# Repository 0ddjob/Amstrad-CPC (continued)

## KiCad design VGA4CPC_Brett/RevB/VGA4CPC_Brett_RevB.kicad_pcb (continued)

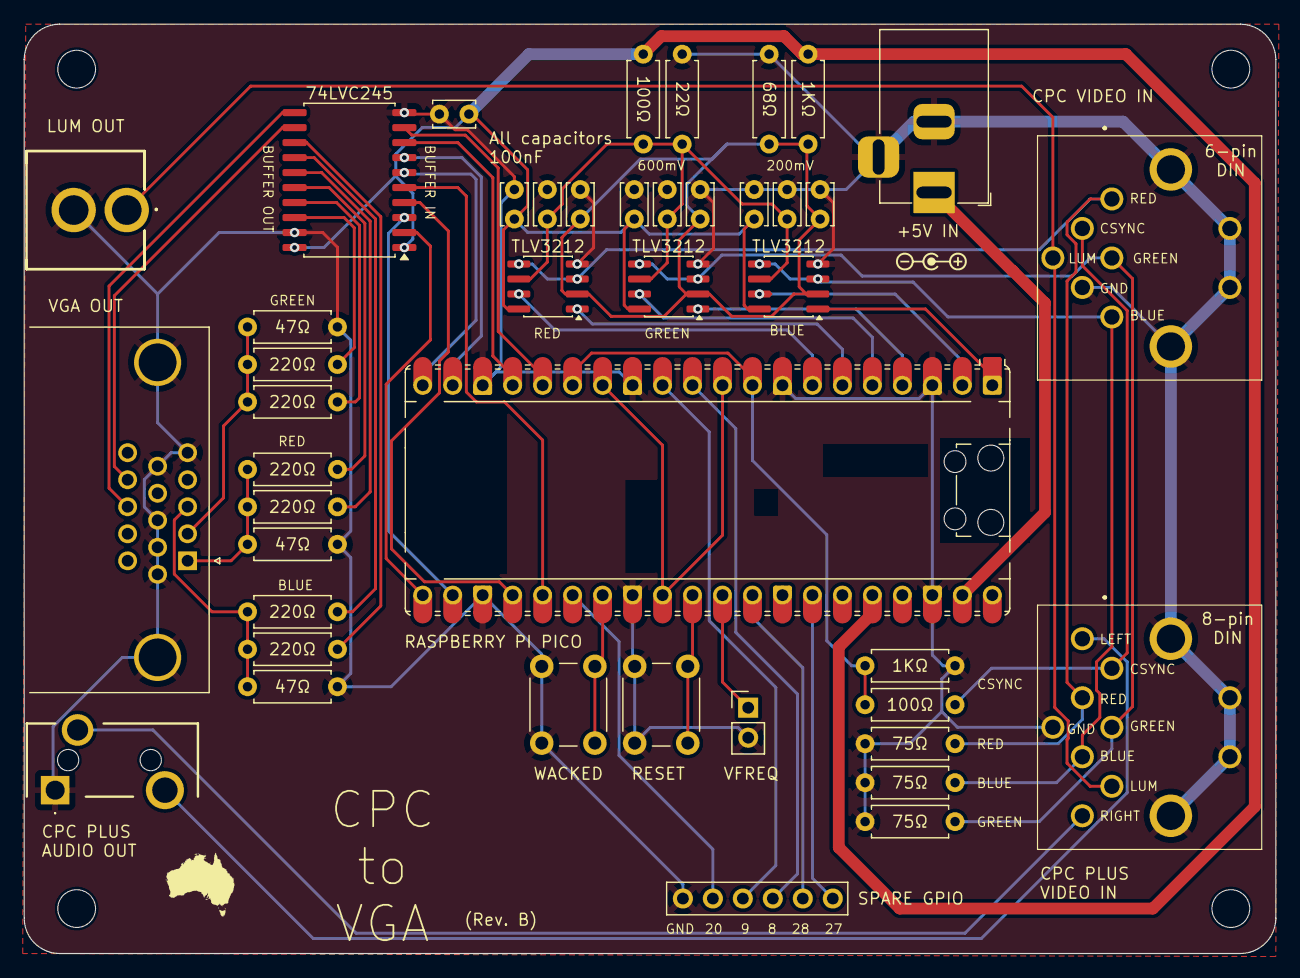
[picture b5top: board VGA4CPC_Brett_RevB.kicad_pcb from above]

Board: 2 copper layers, 106.0 x 78.7 mm, 47 parts (0 on the bottom side), 47 nets.

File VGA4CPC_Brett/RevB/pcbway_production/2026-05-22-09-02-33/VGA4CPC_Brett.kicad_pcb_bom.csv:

Designator,Quantity,Value,Footprint,Package,MPN,DNP,Mount_Type,Description,Height,Mouser Part Number,Mouser Price/Stock,Manufacturer_Name
"C1, C10, C2, C3, C4, C5, C6, C7, C8, C9",10,100nF,C_Disc_D3.4mm_W2.1mm_P2.50mm,,,,tht,,,,,
"H1, H2, H3, H4",4,MountingHole,MountingHole_3.2mm_M3,,,,tht,,,,,
J1,1,+5V IN,BarrelJack_Horizontal,,,,tht,DC Barrel Jack,,,,
J2,1,CPC PLUS AUDIO OUT,SJ335083ATR,,,,tht,"Audio Jack, 3 Poles (Stereo / TRS)",,,,
J3,1,CPC PLUS VIDEO IN,SDF80J,,,,tht,Same Sky SDF-80J 8-pin DIN socket,,,,
J4,1,CPC VIDEO IN,SDF80J,,,,tht,Same Sky SDF-60J 6-pin DIN Socket,,,,
J5,1,VFREQ,PinHeader_1x02_P2.54mm_Vertical,,,,tht,"Generic connector, single row, 01x02, script generated (kicad-library-utils/schlib/autogen/connector/)",,,,
J6,1,VGA OUT,DSUB-15-HD_Socket_Horizontal_P2.29x2.54mm_EdgePinOffset8.35mm_Housed_MountingHolesOffset10.89mm,,,,tht,"15-pin D-SUB connector, socket (female), High density (3 columns), Triple Row, Generic, VGA-connector, Mounting Hole",,,,
J7,1,LUM OUT,1560099E,,,,tht,"coaxial connector (BNC, SMA, SMB, SMC, Cinch/RCA, LEMO, ...)",,,,
"R1, R7",2,1KΩ,R_Axial_DIN0207_L6.3mm_D2.5mm_P7.62mm_Horizontal,,,,tht,"Resistor, small symbol",,,,
"R10, R12, R13, R15, R16, R18",6,220Ω,R_Axial_DIN0207_L6.3mm_D2.5mm_P7.62mm_Horizontal,,,,tht,"Resistor, small symbol",,,,
"R11, R14, R17",3,47Ω,R_Axial_DIN0207_L6.3mm_D2.5mm_P7.62mm_Horizontal,,,,tht,"Resistor, small symbol",,,,
"R2, R6",2,100Ω,R_Axial_DIN0207_L6.3mm_D2.5mm_P7.62mm_Horizontal,,,,tht,"Resistor, small symbol",,,,
R3,1,68Ω,R_Axial_DIN0207_L6.3mm_D2.5mm_P7.62mm_Horizontal,,,,tht,"Resistor, small symbol",,,,
R4,1,22Ω,R_Axial_DIN0207_L6.3mm_D2.5mm_P7.62mm_Horizontal,,,,tht,"Resistor, small symbol",,,,
"R5, R8, R9",3,75Ω,R_Axial_DIN0207_L6.3mm_D2.5mm_P7.62mm_Horizontal,,,,tht,"Resistor, small symbol",,,,
SW1,1,RESET,SW_PUSH_6mm,,,,tht,"Push button switch, generic, two pins",,,,
"U1, U2, U4",3,TLV3202AID,SOIC-8_3.9x4.9mm_P1.27mm,,TLV3202AID,,smt,"Dual, 40ns, microPower, Rail-to-Rail input  Comparator with Push-pull outputs",1.75,595-TLV3202AID,https://www.mouser.co.uk/ProductDetail/Texas-Instruments/TLV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,Texas Instruments
U3,1,RASPBERRY PI PICO,RaspberryPi_Pico_Common_Unspecified,,,,tht,"Versatile and inexpensive microcontroller module powered by RP2040 dual-core Arm Cortex-M0+ processor up to 133 MHz, 264kB SRAM, 2MB QSPI flash; also supports Raspberry Pi Pico 2",,,,
U5,1,74LVC245,SOIC-20W_7.5x12.8mm_P1.27mm,,,,smt,"Octal BUS Transceivers, 3-State outputs",,,,

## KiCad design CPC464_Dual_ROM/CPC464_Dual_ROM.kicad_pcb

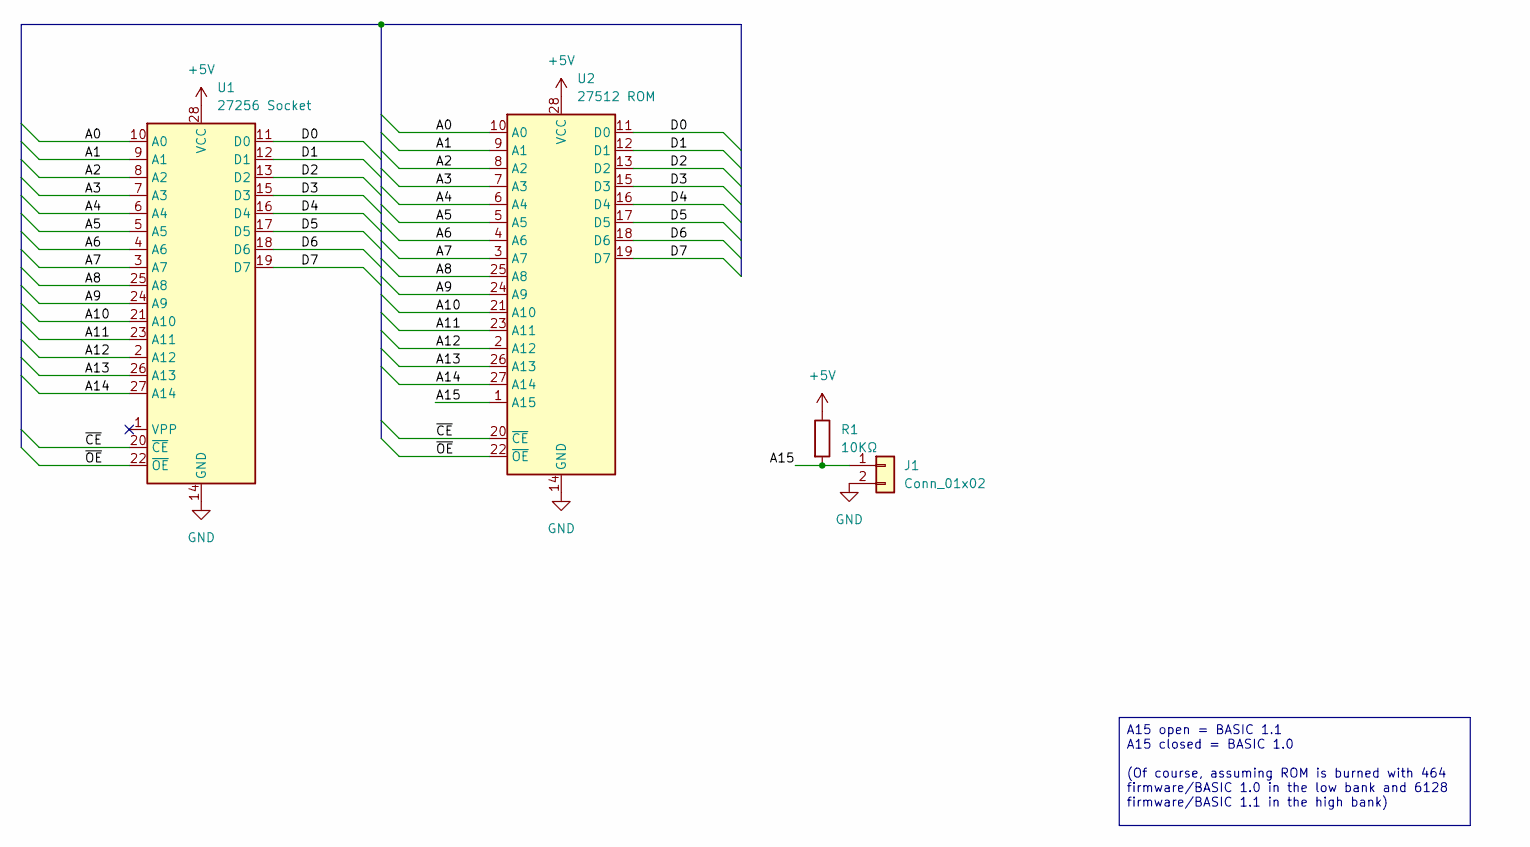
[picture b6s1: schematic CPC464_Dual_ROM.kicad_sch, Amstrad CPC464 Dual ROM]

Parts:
J1: Conn_01x02; PinHeader_1x02_P2.54mm_Vertical
R1: 10KΩ; R_Axial_DIN0207_L6.3mm_D2.5mm_P7.62mm_Horizontal
U1: 27256 Socket; DIP-28_W15.24mm
U2: 27512 ROM; DIP-28_W15.24mm_Socket

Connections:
+5V: R1.1, U1.28 (VCC), U2.28 (VCC)
/A0: U1.10 (A0), U2.10 (A0)
/A1: U1.9 (A1), U2.9 (A1)
/A2: U1.8 (A2), U2.8 (A2)
/A3: U1.7 (A3), U2.7 (A3)
/A4: U1.6 (A4), U2.6 (A4)
/A5: U1.5 (A5), U2.5 (A5)
/A6: U1.4 (A6), U2.4 (A6)
/A7: U1.3 (A7), U2.3 (A7)
/A8: U1.25 (A8), U2.25 (A8)
/A9: U1.24 (A9), U2.24 (A9)
/A10: U1.21 (A10), U2.21 (A10)
/A11: U1.23 (A11), U2.23 (A11)
/A12: U1.2 (A12), U2.2 (A12)
/A13: U1.26 (A13), U2.26 (A13)
/A14: U1.27 (A14), U2.27 (A14)
/A15: J1.1, R1.2, U2.1 (A15)
/D0: U1.11 (D0), U2.11 (D0)
/D1: U1.12 (D1), U2.12 (D1)
/D2: U1.13 (D2), U2.13 (D2)
/D3: U1.15 (D3), U2.15 (D3)
/D4: U1.16 (D4), U2.16 (D4)
/D5: U1.17 (D5), U2.17 (D5)
/D6: U1.18 (D6), U2.18 (D6)
/D7: U1.19 (D7), U2.19 (D7)
/~CE: U1.20 (~CE), U2.20 (~CE)
/~OE: U1.22 (~OE), U2.22 (~OE)
GND: J1.2, U1.14 (GND), U2.14 (GND)

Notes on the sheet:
A15 open = BASIC 1.1 A15 closed = BASIC 1.0 (Of course, assuming ROM is burned with 464 firmware/BASIC 1.0 in the low bank and 6128 firmware/BASIC 1.1 in the high bank)

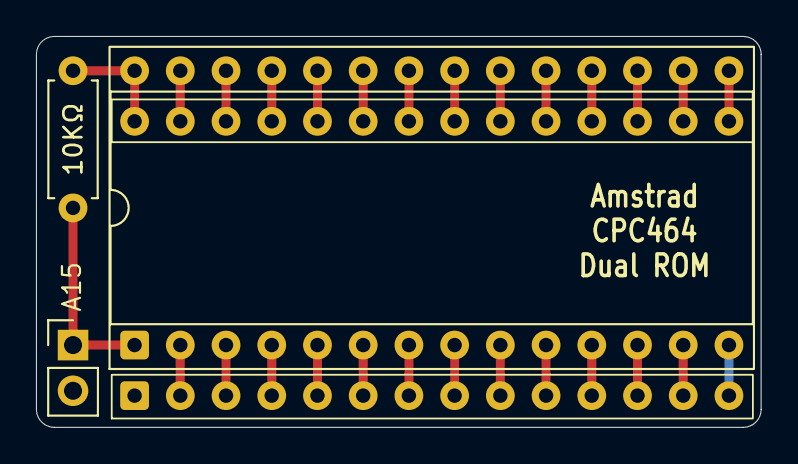
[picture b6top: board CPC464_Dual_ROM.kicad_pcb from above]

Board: 2 copper layers, 40.3 x 21.7 mm, 4 parts (0 on the bottom side), 28 nets.

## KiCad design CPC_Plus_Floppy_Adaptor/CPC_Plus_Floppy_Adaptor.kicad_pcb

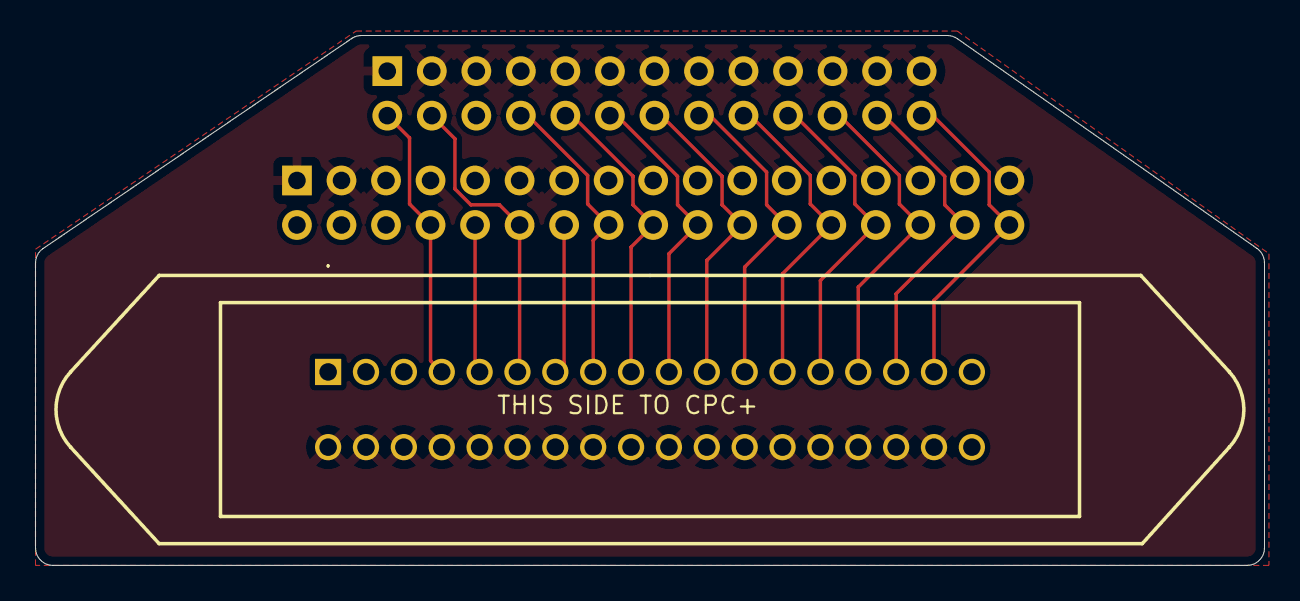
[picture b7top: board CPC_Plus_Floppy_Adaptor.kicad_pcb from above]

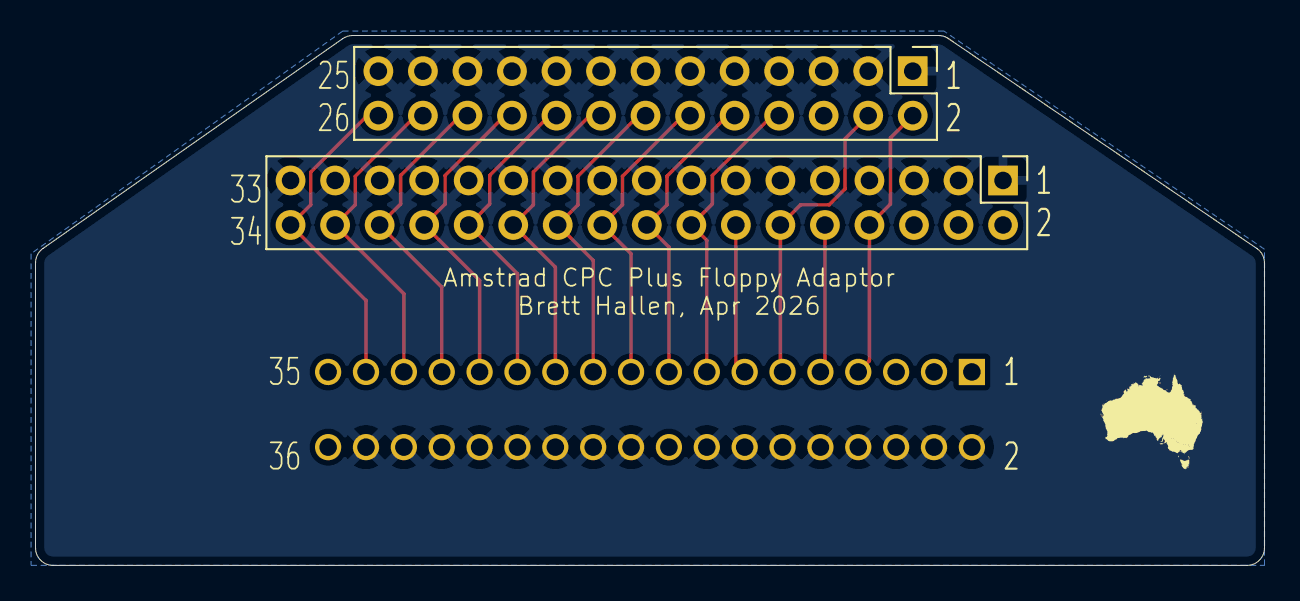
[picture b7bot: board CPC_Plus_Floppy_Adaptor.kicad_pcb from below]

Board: 2 copper layers, 70.1 x 30.2 mm, 3 parts (2 on the bottom side), 15 nets.

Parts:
J1: 111-036-113L001
J2: Standard Floppy; PinHeader_2x17_P2.54mm_Vertical
J3: CPC Floppy; PinHeader_2x13_P2.54mm_Vertical

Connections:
/~DIR: J1.17, J2.18, J3.10
/~DRVSA: J1.13, J2.14
/~DRVSB: J1.11, J2.12, J3.4
/~INDEX: J1.7, J2.8, J3.2
/~MOTEA: J1.9, J2.10
/~MOTEB: J1.15, J2.16, J3.8
/~RDATA: J1.29, J2.30, J3.22
/~RDY: J1.33, J2.34, J3.26
/~SIDE1: J1.31, J2.32, J3.24
/~STEP: J1.19, J2.20, J3.12
/~TRK00: J1.25, J2.26, J3.18
/~WDATA: J1.21, J2.22, J3.14
/~WGATE: J1.23, J2.24, J3.16
/~WPT: J1.27, J2.28, J3.20
GND: J1.2, J1.4, J1.6, J1.8, J1.10, J1.12, J1.14, J1.16, J1.20, J1.22, J1.24, J1.26, J1.28, J1.30, J1.32, J1.34, J2.1, J2.3, J2.5, J2.7, J2.9, J2.11, J2.13, J2.15, J2.17, J2.19, J2.21, J2.23, J2.25, J2.27, J2.29, J2.31, J2.33, J3.1, J3.3, J3.5, J3.7, J3.9, J3.11, J3.13, J3.15, J3.17, J3.19, J3.21, J3.23, J3.25

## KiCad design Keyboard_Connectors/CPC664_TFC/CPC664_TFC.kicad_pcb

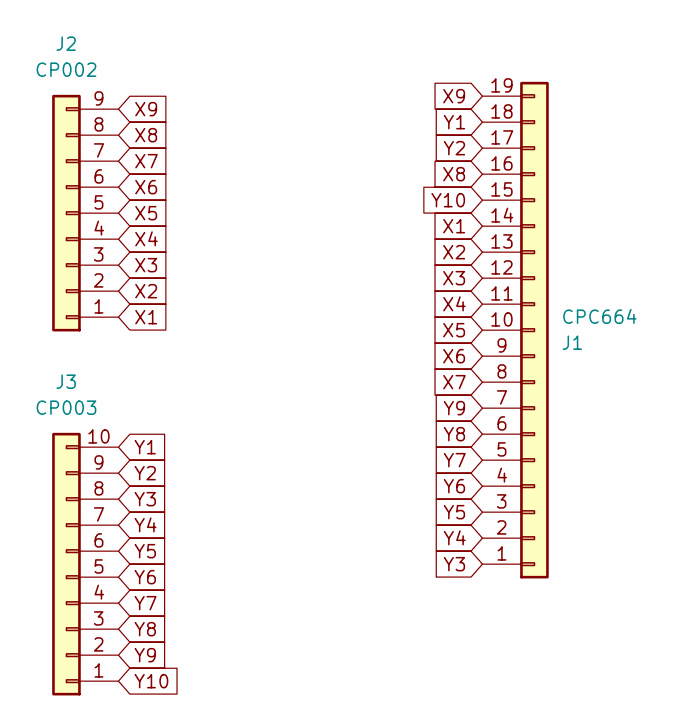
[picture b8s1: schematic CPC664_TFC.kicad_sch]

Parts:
J1: CPC664; Amstrad_CPC664_Keyboard
J2: CP002; PinHeader_1x09_P2.54mm_Vertical_SMD_Pin1Left
J3: CP003; PinHeader_1x10_P2.54mm_Vertical_SMD_Pin1Left

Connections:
X1: J1.14, J2.1
X2: J1.13, J2.2
X3: J1.12, J2.3
X4: J1.11, J2.4
X5: J1.10, J2.5
X6: J1.9, J2.6
X7: J1.8, J2.7
X8: J1.16, J2.8
X9: J1.19, J2.9
Y1: J1.18, J3.10
Y2: J1.17, J3.9
Y3: J1.1, J3.8
Y4: J1.2, J3.7
Y5: J1.3, J3.6
Y6: J1.4, J3.5
Y7: J1.5, J3.4
Y8: J1.6, J3.3
Y9: J1.7, J3.2
Y10: J1.15, J3.1

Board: 2 copper layers, 3 parts (0 on the bottom side), 19 nets, no tracks yet.

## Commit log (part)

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2025-07-24 Started CPC6128 keyboard design
2025-07-24 CPC6128 keyboard updates
2025-07-30 Reorganise CPC projects
2025-07-30 Finalising 12mm tactile design
2025-07-30 Consolidating Amstrad CPC projects
2025-07-31 Finalised Rev. A of tactile keyboard design
2025-08-01 Added 6mm tactile design
2026-05-20 Reorient PCB text
2026-05-21 Create RevA version
2026-05-21 Create Rev. B version
    [1] Added buffer on Pico VGA output signals as suggested by WacKEDmaN
    [2] Added RCA jack for luminosity (B&W) signal pass-through
2026-05-21 Added BOM to schematic
2026-05-22 Silkscreen updates
2026-05-22 Spare GPIO ports routed
    [1] Additional WACKED button (GPIO 21) for "future use"
    [2] Spare GPIO 8/9/20 brought out to pin header for "future use"
2026-05-22 Broke out extra spare GPIO ports
2026-05-24 Reorganise RevA & RevB
2026-05-24 CPC-only RevC small PCB
    Under 100x100mm so US$5 for 10 PCBs
2026-05-24 Added +3.3V on spare GPIO header
2026-05-24 Updated 3D image
2026-05-24 Corrected RevC in schematic sheet
2026-05-24 Added CPC PLUS connectors
    [1] 8-pin DIN for CPC PLUS
    [2] pass-through of CPC PLUS audio
2026-05-24 Initial commit
    Nothing fancy, simply converts CPC DIN connector to VGA for easier connecting to something else, no fancy signal conditioning
    Or, simply use the B&W LUM output
    Also exposes the CPC PLUS stereo audio
2026-05-24 Type correction
2026-05-30 TLV3212 -> TLV3232
    Had to change footprint from SOIC-8 to SSOP-8
2026-05-30 Updated PCB text to "15KHz VGA OUT"
2026-05-30 Added "15KHz VGA" note to PCB
2026-05-30 New comparator daughterboard for Rev. F design
    Moved comparators to separate daughterboard to simplify main VGA board design
2026-05-30 Widened the PCB
    Made more room on the PCB in case we want to change it and not have to change the footprint on the main board.
2026-05-31 Rev. F initial commit
    Moved comparator to own daughterboard
    Switched from 3.3V to 5V logic (requires Pico 2 for sure)
    Switched 74LVC245 (SMD) to 74HCT245 (through-hole)
2026-06-24 Further tweaks to HOUSE2.BAS
    Added REMmarks for each section
2026-06-24 Update HauntedHouse.dsk
    Tweaked CARRYING? verb output to avoid extra comma at the end
2026-06-25 Updated DSK image
    [1] Tweaked HOUSE2.BAS
    [2] Added README.BAS
2026-06-25 Initial commit - work in progress
    Dungeon Designer working
    DUNGEON1.BAS is the straight conversion of the original
    DUNGEON2.BAS has tweaks & improvements
2026-06-25 Added BASIC file listings
2026-06-25 Initial commit of completed conversions
2026-06-26 Error for semicolon instead of colon
    For example:
    PRINT;PRINT"xxxx" (error)
    PRINT:PRINT"xxxx" (ok)
2026-06-26 Remove PDFs
    Still available from Usborne!
